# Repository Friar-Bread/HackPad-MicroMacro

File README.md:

# HackPad-MicroMacro
Blueprint project of a hackpad to be used with my computer for gaming, coding and audio work.

Simple but versatile hackpad

Didn't want to learn fusion so I used Onshape but I did learn KiCAD which was fun

For now buttons are just for volume and copy/paste
Eventually I want to add midi functionality to work as a controller for a dm7 sound board
- This would allow me to make a "go" button that reacts with LEDs for theatrical sound

I also want to add light up functionality for things like caps lock and animations but for now I wanted less distractions from the main design

I'm not a programmer but i tried :D

BOM:
- 4x Cherry MX Switches
- 12x SK6812 MINI LEDs
- 1x XIAO RP2040
- 4x Blank DSA Keycaps (White)
- 4x M3x16 Bolts
- 4x M3 Heatset Inserts
- 1x Printed Base
- 1x Printed Lid

CAD: done in onshape

Schematic: KiCAD

PCB: KiCAD

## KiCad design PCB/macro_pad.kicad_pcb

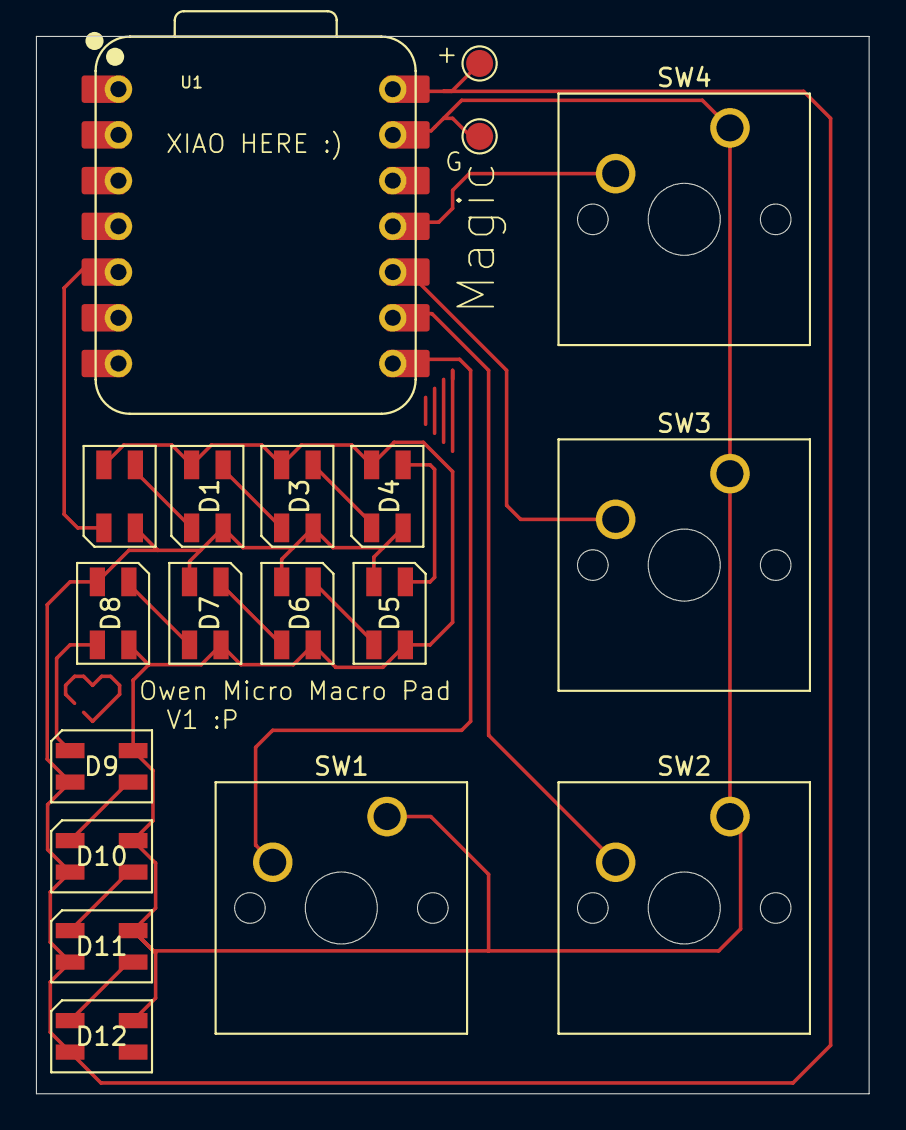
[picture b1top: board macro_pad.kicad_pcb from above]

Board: 2 copper layers, 46.3 x 58.7 mm, 19 parts (0 on the bottom side), 18 nets.

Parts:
D1, D2, D3, D4, D5, D6, D7, D8, D9, D10, D11, D12: SK6812MINI; LED_SK6812MINI_PLCC4_3.5x3.5mm_P1.75mm
SW1, SW2, SW3, SW4: SW_Push; SW_Cherry_MX_1.00u_PCB
TP1, TP2: TestPoint; TestPoint_Pad_D1.5mm
U1: XIAO-RP2040-DIP

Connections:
+5V: D1.4 (VDD), D2.4 (VDD), D3.4 (VDD), D4.4 (VDD), D5.4 (VDD), D6.4 (VDD), D7.4 (VDD), D8.4 (VDD), D9.4 (VDD), D10.4 (VDD), D11.4 (VDD), D12.4 (VDD), TP1.1, U1.14 (VBUS)
GND: D1.2 (VSS), D2.2 (VSS), D3.2 (VSS), D4.2 (VSS), D5.2 (VSS), D6.2 (VSS), D7.2 (VSS), D8.2 (VSS), D9.2 (VSS), D10.2 (VSS), D11.2 (VSS), D12.2 (VSS), SW1.1, SW2.1, SW3.1, SW4.1, TP2.1, U1.13 (GND)
unnamed: D1.3 (DIN), D2.1 (DOUT)
unnamed: D1.1 (DOUT), D3.3 (DIN)
unnamed: D2.3 (DIN), U1.5 (GPIO6/SDA)
unnamed: D3.1 (DOUT), D4.3 (DIN)
unnamed: D4.1 (DOUT), D5.3 (DIN)
unnamed: D5.1 (DOUT), D6.3 (DIN)
unnamed: D6.1 (DOUT), D7.3 (DIN)
unnamed: D7.1 (DOUT), D8.3 (DIN)
unnamed: D8.1 (DOUT), D9.3 (DIN)
unnamed: D9.1 (DOUT), D10.3 (DIN)
unnamed: D10.1 (DOUT), D11.3 (DIN)
unnamed: D11.1 (DOUT), D12.3 (DIN)
unnamed: SW1.2, U1.8 (GPIO1/RX)
unnamed: SW2.2, U1.9 (GPIO2/SCK)
unnamed: SW4.2, U1.11 (GPIO3/MOSI)
unnamed: SW3.2, U1.10 (GPIO4/MISO)

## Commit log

2025-11-30 Read me and other files
2025-11-30 reorganization and code
2025-11-30 readme changes
2025-11-30 fixed images
2025-11-30 fixed images real
